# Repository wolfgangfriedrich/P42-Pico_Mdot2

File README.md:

# P42 Pico M.2

A RPi Pico RP2350A microcontroller board in m.2 3024 form factor with A and E key. The m.2 interface has USB, UART, I2C and control IO connectivity. Voltage levels for the m.2 specification are obeyed as some of the interfaces run on 1.8 V. Externally, +3.3 V, GND, the SWD interface and 16 IOs are accessible on castellated pins. A footprint for a QWIIC connector is on the top side of the board, not populated to have the board as low profile as possible. Power rail LEDs and a user controlled LED is on board, as well as a solder bridge for configuration options. Bottom side has a micro-SD card slot for data storage.
A microcontroller could give any host computer flexible and excellent real-time IO and data processing capabilities. The RPi Pico with its programmable PIO interface has excellent timing resolution. 

### Pre-order campaign on Lectronz https://lectronz.com/campaigns/pre-order-p42-pico2-m-2

Full Feature List:
*	M.2 2230-D5-AE card (22 mm x 30 mm; D5 = 1.5mm on top and bottom side violated by the QWIIC connector and the bottom SD card holder; A and E key)
*	Used interfaces on the M.2: USB, UART, I2C, ALERT, WAKE, DISABLE1/2, LED 1/2, VENDOR_DEFINED
*	1.8V regulator for level-shifters
*	Power LEDs for 3.3 V and 1.1 V
*	RP2040/RP2350 peripherals: 2 MB Flash, SWD debug access, RESET and BOOTSEL button, 
*	QWIIC connector, 1 LED, 1 solder bridge for configuration, 16 GPIOs on castellated pins
*	castellated pins on 25.4 mm/0.1" raster (almost with a 22 mm board)
*	optional uSD card holder on the bottom side
*	optional pull-down resistors on castellated IOs to mitigate the E9 Erratum

Main Components
*	Microcontroller RaspberryPi RP2350A
*	16Mbit QSPI Flash W25Q16
*	12 MHz Crystal SMD_3225-4Pin_3.2x2.5mm
*	MicroSD card holder Molex 104031-0811
*	1.8V-3.3V High Speed level shifter Texas Instruments TXS0102DQM

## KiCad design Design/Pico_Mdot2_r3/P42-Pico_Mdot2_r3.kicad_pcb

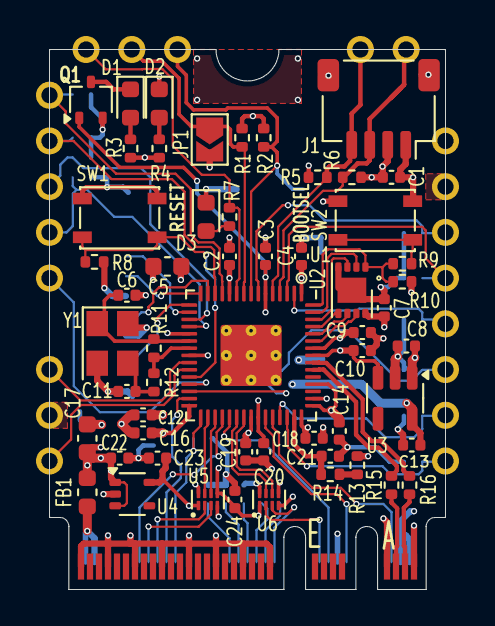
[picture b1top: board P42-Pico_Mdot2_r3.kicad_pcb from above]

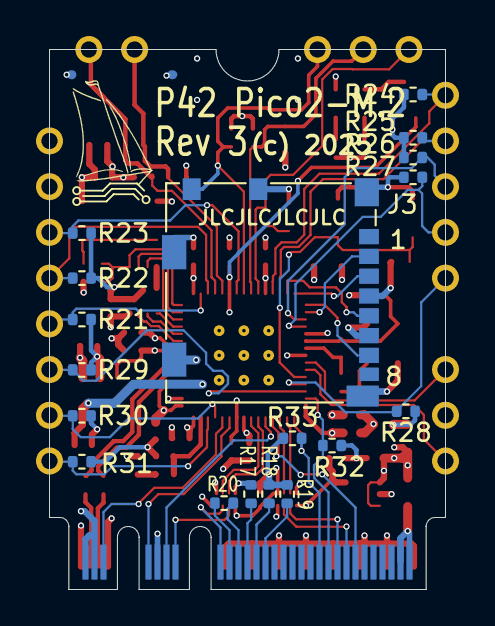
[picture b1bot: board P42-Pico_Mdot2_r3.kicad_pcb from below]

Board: 4 copper layers, 22.0 x 30.0 mm, 95 parts (18 on the bottom side), 67 nets.

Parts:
C1, C2, C3, C4, C7, C9, C10, C12, C14, C16, C18, C19, C20, C24: 1uF; C_0402_1005Metric
C5, C17: 10u; C_0603_1608Metric
C6, C11: 27p; C_0402_1005Metric
C8, C13, C21, C22, C23: 2.2u; C_0402_1005Metric
D1, D2: Yellow; LED_0603_1608Metric
D3: Green; LED_0603_1608Metric
FB1: 600R/0.5A; L_0603_1608Metric
J1: QWIIC; JST_SH_SM04B-SRSS-TB_1x04-1MP_P1.00mm_Horizontal
J2: Bus_M.2_Socket_AE; NGFF_A+E
J3: Micro_SD_Card_Det2; microSD_HC_Molex_104031-0811
JP1: Enable; SolderJumper-2_P1.3mm_Open_TrianglePad1.0x1.5mm
Q1: RJU003N03; SOT-323_SC-70
R1, R2, R5, R6, R8, R10, R17, R18, R19, R21, R22, R23, R24, R25, R26, R27, R28, R29, R30, R31, R32, R33: 47K0; R_0402_1005Metric
R3, R4, R7: 10K0; R_0402_1005Metric
R9, R12, R13: 1K0; R_0402_1005Metric
R11: 1 MEG; R_0402_1005Metric
R14, R15, R16, R20: 10R; R_0402_1005Metric
SW1: RESET; SW_SPST_PTS810
SW2: BOOTSEL; SW_SPST_PTS810
TP1, TP2, TP3, TP6, TP8, TP9, TP11, TP12, TP13, TP14, TP15, TP17, TP19, TP21: TestPoint; THTPad_D1.5mm_Drill0.9mm
TP4: Q_SCL; THTPad_D1.5mm_Drill0.9mm
TP5: Q_SDA; THTPad_D1.5mm_Drill0.9mm
TP7: +3V3; THTPad_D1.5mm_Drill0.9mm
TP10, TP18: GND; THTPad_D1.5mm_Drill0.9mm
TP16: SWCLK; THTPad_D1.5mm_Drill0.9mm
TP20: SWD; THTPad_D1.5mm_Drill0.9mm
U1: W25Q16; SON-8-1EP_3x2mm_P0.5mm_EP1.4x1.6mm
U2: RP2350IO_60QFN; RP2350-QFN-60-1EP_7x7_P0.4mm_EP3.4x3.4mm_ThermalVias
U3: LDO-1.1; SOT-23-5
U4: AP2125KS-1.8; SOT-353_SC-70-5
U5, U6: TXS0102DQE; X2SON-8_1.4x1mm_P0.35mm
Y1: 12 MHz; Crystal_SMD_3225-4Pin_3.2x2.5mm

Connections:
+1V1: C3.1, C12.1, C13.1, C20.1, Q1.1 (G), U2.6 (DVDD), U2.23 (DVDD), U2.39 (DVDD), U3.5 (VOUT)
+1V8: C23.1, C24.1, U4.5 (VOUT), U5.1 (VCCA), U5.5 (OE), U6.1 (VCCA), U6.5 (OE)
+3V3: C1.1, C2.1, C4.1, C5.1, C7.1, C8.1, C9.1, C10.1, C14.1, C16.1, C17.1, C18.1, C19.1, C22.1, FB1.1, J1.2, J3.4 (VDD), R1.2, R2.1, R3.1, R4.1, R5.2, R6.2, R8.2, R10.2, R13.2, R17.1, TP7.1, U1.8 (VCC), U2.1 (IOVDD), U2.11 (IOVDD), U2.20 (IOVDD), U2.30 (IOVDD), U2.38 (IOVDD), U2.45 (IOVDD), U2.46 (VREG_AVDD), U2.49 (VREG_VIN), U2.53 (USB_OTP_VDD), U2.54 (QSPI_IOVDD), U3.1 (VIN), U3.3 (EN), U4.1 (VIN), U4.3 (EN), U5.8 (VCCB), U6.8 (VCCB)
/Pico/ADC_VREF: R13.1, R14.2
/Pico/EN: JP1.1 (A), R1.1, TP2.1, U2.9 (I2C1DA_SPI0CK_GPIO6)
/Pico/GP0: R21.2, TP15.1, U2.2 (UART0TX_I2C0DA_SPI0RX_GPIO0)
/Pico/GP1: R22.2, TP14.1, U2.3 (UART0RX_I2C0CL_SPI0CSn_GPIO1)
/Pico/GP4: R23.2, TP12.1, U2.7 (UART1TX_I2C0DA_SPI0RX_GPIO4)
/Pico/GP8: R24.2, TP6.1, U2.12 (UART1TX_I2C0DA_SPI1RX_GPIO8)
/Pico/GP9: R25.2, TP8.1, U2.13 (UART1RX_I2C0CL_SPI1CSn_GPIO9)
/Pico/GP14: R26.2, TP9.1, U2.18 (I2C1DA_SPI1CK_GPIO14)
/Pico/GP15: R27.2, TP11.1, U2.19 (I2C1CL_SPI1TX_GPIO15)
/Pico/GP16: R28.2, TP13.1, U2.27 (UART0TX_I2C0DA_SPI0RX_GPIO16)
/Pico/GP17: R29.2, TP17.1, U2.28 (UART0RX_I2C0CL_SPI0CSn_GPIO17)
/Pico/GP28: R30.2, TP19.1, U2.42 (UART0TX_I2C0DA_SPI1RX_GPIO28_ADC2)
/Pico/GP29: R31.2, TP21.1, U2.43 (UART0RX_I2C0CL_SPI1CSn_GPIO29_ADC3)
/Pico/I2C_SCL: U2.33 (UART1RX_I2C0CL_SPI0CSn_GPIO21), U5.6 (B2)
/Pico/I2C_SDA: U2.32 (UART1TX_I2C0DA_SPI0RX_GPIO20), U5.7 (B1)
/Pico/LED: R7.1, TP1.1, U2.10 (I2C1CL_SPI0TX_GPIO7)
/Pico/QSCLK: U1.6 (CLK), U2.56 (QSPI_SCLK)
/Pico/QSD0: U1.5 (DI(IO0)), U2.57 (QSPI_SD0)
/Pico/QSD1: U1.2 (DO(IO1)), U2.59 (QSPI_SD1)
/Pico/QSD2: U1.3 (IO2), U2.58 (QSPI_SD2)
/Pico/QSD3: U1.7 (IO3), U2.55 (QSPI_SD3)
/Pico/SWCLK: TP16.1, U2.24 (SWCLK)
/Pico/SWD: TP20.1, U2.25 (SWD)
/Pico/UART_RXD: U2.37 (UART1RX_I2C0CK_SPI1CSn_GPIO25), U6.6 (B2)
/Pico/UART_TXD: U2.36 (UART1TX_I2C0DA_SPI1RX_GPIO24), U6.7 (B1)
/Pico/USB+: J2.3 (USB_D+), R16.1
/Pico/USB-: J2.5 (USB_D-), R15.1
/Pico/USB_D+: R16.2, U2.52 (USB_DP)
/Pico/USB_D-: R15.2, U2.51 (USB_DM)
/Pico/XI: C6.1, R11.1, U2.21 (XIN), Y1.1
/Pico/XO: R11.2, R12.2, U2.22 (XOUT)
/Pico/XXO: C11.1, R12.1, Y1.3
/Pico/nDIS1: J2.56 (~W_DISABLE1), R32.2, U2.29 (I2C1DA_SPI0CK_GPIO18)
/Pico/nDIS2: J2.54 (~W_DISABLE2), R33.2, U2.31 (I2C1CK_SPI0TX_GPIO19)
/Pico/nQSS: R9.1, R10.1, U1.1 (~CS), U2.60 (QSPI_SS)
/Pico/nRESET: R8.1, SW1.2 (B), U2.26 (RUN)
/Pico/~I2C_ALERT: J2.62 (~ALERT), U2.34 (UART_I2C1DA_SPI0CK_GPIO22)
/Pico/~LED1: J2.6 (~LED_1), U2.41 (UART_I2C1CL_SPI1TX_GPIO27_ADC1)
/Pico/~LED2: J2.16 (~LED_2), U2.40 (UART_I2C1DA_SPI1CK_GPIO26_ADC0)
/Pico/~UART_WAKE: J2.20 (~UART_WAKE), U2.35 (UART_I2C1CK_SPI0TX_GPIO23)
/QWIIC_SCL: J1.4, R5.1, TP4.1, U2.5 (I2C1CL_SPI0TX_GPIO3)
/QWIIC_SDA: J1.3, R6.1, TP5.1, U2.4 (I2C1DA_SPI0CL_GPIO2)
/RXD_18: J2.32 (UART_TXD), U6.3 (A2)
/SD_CLK: J3.5 (CLK), U2.14 (I2C1DA_SPI1CK_GPIO10)
/SD_CS: J3.2 (DAT3/CD), U2.17 (UART0RX_I2C0CL_SPI1CSn_GPIO13)
/SD_DET: J3.10 (DET_A), R2.2, TP3.1, U2.8 (UART1RX_I2C0CL_SPI0CSn_GPIO5)
/SD_DI: J3.7 (DAT0), U2.16 (UART0TX_I2C0DA_SPI1RX_GPIO12)
/SD_DO: J3.3 (CMD), U2.15 (I2C1CK_SPI1TX_GPIO11)
/TXD_18: J2.22 (UART_RXD), U6.2 (A1)
GND: C1.2, C2.2, C3.2, C4.2, C5.2, C6.2, C7.2, C8.2, C9.2, C10.2, C11.2, C12.2, C13.2, C14.2, C16.2, C17.2, C18.2, C19.2, C20.2, C21.2, C22.2, C23.2, C24.2, D2.1 (K), D3.1 (K), J1.1, J2.1 (GND), J2.7 (GND), J2.18 (GND), J2.33 (GND), J2.39 (GND), J2.45 (GND), J2.51 (GND), J2.57 (GND), J2.63 (GND), J2.69 (GND), J2.75 (GND), J3.6 (VSS), J3.9 (DET_B), J3.11 (SHIELD), JP1.2 (B), Q1.2 (S), R18.1, R19.1, R21.1, R22.1, R23.1, R24.1, R25.1, R26.1, R27.1, R28.1, R29.1, R30.1, R31.1, R32.1, R33.1, SW1.1 (A), SW2.1 (A), TP10.1, TP18.1, U1.4 (GND), U1.9 (EP), U2.47 (VREG_PGND), U2.61 (GND), U3.2 (GND), U4.2 (GND), U5.4 (GND), U6.4 (GND), Y1.2, Y1.4
unnamed: D1.2 (A), R3.2
unnamed: D1.1 (K), Q1.3 (D)
unnamed: D2.2 (A), R4.2
unnamed: D3.2 (A), R7.2
unnamed: FB1.2, J2.2 (3.3V), J2.4 (3.3V), J2.72 (3.3V), J2.74 (3.3V)
unnamed: J2.60 (I2C_CLK), U5.3 (A2)
unnamed: J2.58 (I2C_DATA), U5.2 (A1)
unnamed: J2.34 (UART_CTS), R20.1
unnamed: J2.36 (UART_RTS), R20.2
unnamed: J2.38 (VENDOR_DEFINED), R17.2
unnamed: J2.40 (VENDOR_DEFINED), R18.2
unnamed: J2.42 (VENDOR_DEFINED), R19.2
unnamed: R9.2, SW2.2 (B)
unnamed: C21.1, R14.1, U2.44 (ADC_AVDD)

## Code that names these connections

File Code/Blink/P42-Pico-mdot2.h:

// Pico_M.2 header file for all P42-Pico-M.2 projects 
// (c) Pier42 Electronics Design
//     https://www.tindie.com/stores/pier42/


// written by
// Wolfgang Friedrich
// Rev Start 2024/Aug/08
// Last change: 2024/Aug/08

#ifndef P42Pico_mdot2_h
#define P42Pico_mdot2_h

#define PICO_MDOT2_VERSION "0.1"

// Board Features
#define TP15           0
#define TP13           1
#define TP11           2
#define SD_DETECT      3
#define TP3            3
#define QWIIC_SDA      4
#define TP4            4
#define QWIIC_SCL      5
#define TP5            5
#define ENABLE         6
#define TP2            6
#define LED            7
#define TP1            7
#define TP6            8
#define TP8            9
#define SD_CS         10
#define SD_DI         11
#define SD_DO         12
#define SD_CLK        13
#define TP10          14
#define TP12          15
#define UART_TXD      16
#define UART_RXD      17
#define N_DISABLE1    18
#define N_DISABLE2    19
#define I2C_SDA       20
#define I2C_SCL       21
#define N_I2C_ALERT   22
#define N_UART_WAKE   23
#define N_LED2        24
#define N_LED1        25
#define TP14          26
#define TP21          27
#define TP17          28
#define TP19          29

#define ADC0          26
#define ADC1          27
#define ADC2          28
#define ADC3          29



#endif

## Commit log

2025-03-14 Start repo
    No content yet.
2025-03-14 Update README.md
    Add initial info
2025-03-14 Update README.md
    Make it more beautiful.
2025-03-14 Update README.md
    Figured out markdown headlines
2025-03-16 Update .gitignore
    Added more files that nobody shall see.
2025-03-16 Initial data commit
    Design, Code, Documentation
2025-03-16 Delete Code/P42-Pico-mdot2_Tester directory
    only good for rev 1 with RP2040
2025-03-29 Update README.md
    added pre-order campaign
2025-03-29 Add images for web use in \Images folder
2025-04-03 Update P42-Pico_Mdot2_r3.kicad_sch
    Changed power LEDs to yellow
2025-04-09 Update README.md
    Fixed link to pre-order campaign. Thanks to dglaude for noticing.
2025-04-11 Create LICENSE.md
    CERN Open Hardware License Version 2 - Weakly Reciprocal
2025-04-11 SCH update with license
    .kicad_sch sources and PDF docs.
2025-04-11 Update README.md
    Added images of board and pinout
2025-04-11 Create Pico2 M.2 Pinout.jpg
    added for readme
2025-04-11 Update README.md
    typo
2025-04-11 Update README.md
    Pinout picture URL
2025-04-26 Sales units ready
    Up test FW to rev1.0
    Release PCB layout
2025-04-26 Test FW programming file
    Update .uf2
2025-05-05 Update P42 M.2 Pico2 (rev3) Documentation V0.1.pdf
    License update

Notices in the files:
Design/Pico_Mdot2_r3/P42-Pico_Mdot2_r3.kicad_pcb:
(c) 2025 Wolfgang Friedrich
CERN Open Hardware Licence Version 2 - Weakly Reciprocal
(c) 2025
